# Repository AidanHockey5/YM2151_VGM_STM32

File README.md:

# This project has been superseded by...
https://github.com/AidanHockey5/YM2151_Arcade_Classic_2

# YM2151 Arcade Classic

http://www.aidanlawrence.com/ym2151-arcade-classic-adlib-mini/

See this project in action here: https://youtu.be/VlT8aX9DRZw

This project is a hardware Video Game Music (VGM) player that uses a genuine YM2151 FM synthesizer chip. 
This project is driven by an STM32 "Blue Pill" board, chosen for it's ample speed, I/O, and best of all, price!

Included in this repository is the source code for the project, all of the schematic files, a Bill of Materials, and a completed 
Ki-CAD printed circuitboard /w Gerber files. Feel free to produce your own board!

# Information about the main sound chips and VGM

The YM2151 was a popular sound synthesizer for classic arcade systems as well as a few higher-end home computers in the late 80's and early 90's.
This project synthesizes music from .VGM files in real time on genuine hardware. There is no emulation here.

VGM stands for Video Game Music, and it is a 44.1KHz logging format that stores real soundchip register information. My player will parse these files and send the data to the appropriate chips. You can learn more about the VGM file format here: http://www.smspower.org/Music/VGMFileFormat

http://www.smspower.org/uploads/Music/vgmspec170.txt?sid=58da937e68300c059412b536d4db2ca0

# SD Card Information
This project is built for full-sized SD cards, but you may use adapters to fit your desired card. You must format your SD card to Fat32 in order for this device to work correctly. Your SD card must only contain uncompressed .vgm files. VGZ FILES WILL NOT WORK! You may download .vgz files and use [7zip](http://www.7-zip.org/download.html) to extract the uncompressed file out of them. Vgm files on the SD card do not need to have the .vgm extension. As long as they contain valid, uncompressed vgm data, they will be read by the program regardless of their name.
You can find VGM files by Googling "myGameName VGM," or by checking out sites like http://vgmrips.net/packs/

# Control Over Serial
You can use a serial connection to control playback features. The commands are as follows:

Command | Result
------------ | -------------
\+ | Next Track
\- | Previous Track
\* | Random Track
\/ | Toggle Shuffle Mode
\. | Toggle Song Looping
r: | Request song

A song request is formatted as follows: ```r:mySongFile.vgm```
Once a song request is sent through the serial console, an attempt will be made to open that song file. The file must exist on the SD card, and spelling/capitalization must be correct.
Need an easy-to-use serial console? [I've made one here.](https://github.com/AidanHockey5/OpenArduinoSerialConsole)

# Schematic

[PDF](https://github.com/AidanHockey5/YM2151_VGM_STM32/raw/master/Schematic/YM2151_STM32_VGM.pdf)

[Bill Of Materials (BOM)](https://github.com/AidanHockey5/YM2151_VGM_STM32/tree/master/Schematic/BOM)

# KiCad
The schematic and PCB of this project was made in KiCad Version 4.0.7

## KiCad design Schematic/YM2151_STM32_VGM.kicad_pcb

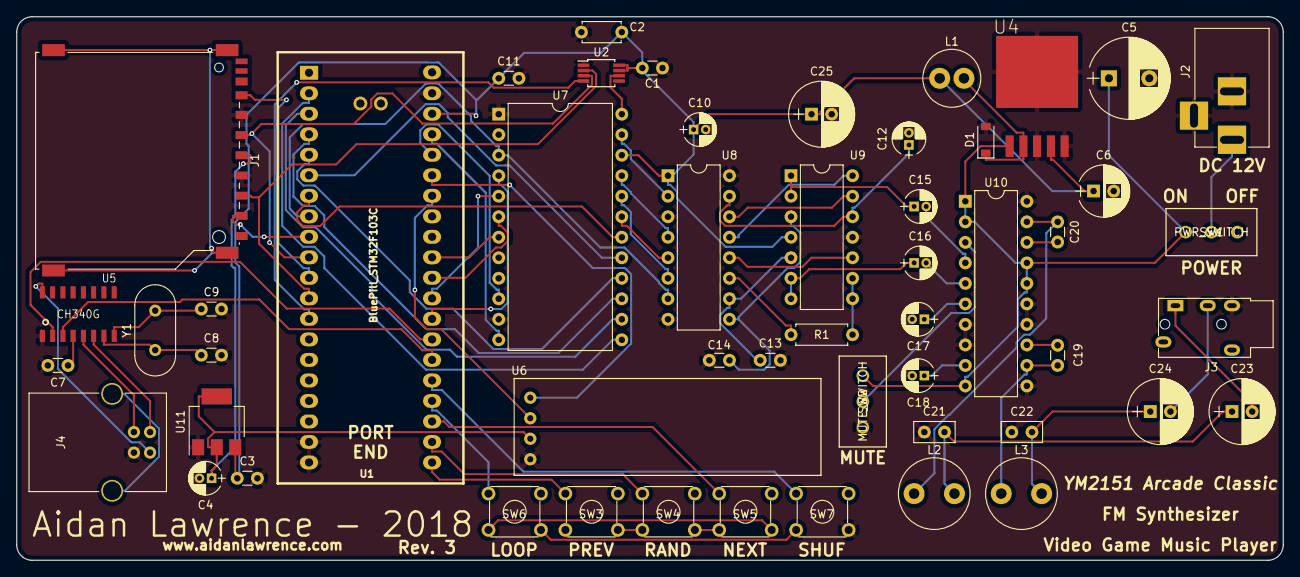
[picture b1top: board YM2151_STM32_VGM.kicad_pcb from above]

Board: 2 copper layers, 156.8 x 67.3 mm, 52 parts (0 on the bottom side), 71 nets.

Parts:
C1: 10nF; C_Disc_D3.0mm_W1.6mm_P2.50mm
C2: 1uF; C_Disc_D4.7mm_W2.5mm_P5.00mm
C3, C7, C11: 100nF; C_Disc_D3.0mm_W1.6mm_P2.50mm
C4, C10, C12: 10uF; CP_Radial_D4.0mm_P1.50mm
C5: 680uF; CP_Radial_D10.0mm_P5.00mm
C6: 220uF; CP_Radial_D6.3mm_P2.50mm
C8, C9: 22pF; C_Disc_D3.0mm_W1.6mm_P2.50mm
C13, C14: 3.3nF; C_Disc_D3.0mm_W1.6mm_P2.50mm
C15, C16, C17, C18: 1uF; CP_Radial_D4.0mm_P1.50mm
C19, C20: 0.22uF; C_Disc_D3.0mm_W1.6mm_P2.50mm
C21, C22: 68nF; C_Disc_D5.0mm_W2.5mm_P2.50mm
C23, C24, C25: 1000uF; CP_Radial_D8.0mm_P2.50mm
D1: SS34; D_SOD-123
J1: SD_Card; SD_TE_2041021
J2: Jack_DC+12V; BARREL_JACK
J3: JACK_TRS_6PINS; PJ320E_3.5mm_Jack
J4: USB_B
L1: 33uH; L_Radial_D7.0mm_P3.00mm
L2, L3: 22uH; L_Radial_D8.7mm_P5.00mm_Fastron_07HCP
R1: 100; R_Axial_DIN0207_L6.3mm_D2.5mm_P7.62mm_Horizontal
SW1: PWR_SWITCH; 1825115-1
SW2: MUTE_SWITCH; 1825115-1
SW3: PREV; SW_TH_Tactile_Omron_B3F-10xx
SW4: RAND; SW_TH_Tactile_Omron_B3F-10xx
SW5: NEXT; SW_TH_Tactile_Omron_B3F-10xx
SW6: LOOP; SW_TH_Tactile_Omron_B3F-10xx
SW7: SHUF; SW_TH_Tactile_Omron_B3F-10xx
U1: BluePill_STM32F103C
U2: LTC6903; MSOP-8_3x3mm_Pitch0.65mm
U4: LM2596S-5.0; TO170P1435X465-6N
U5: CH340G; SOIC16
U6: OLED_128x32_I2C; 128x32_OLED_I2C_Module
U7: YM2151; DIP-24_W15.24mm
U8: YM3012; DIP-16_W7.62mm
U9: TL064; DIP-14_W7.62mm
U10: TPA3122D2; DIP-20_W7.62mm
U11: LD1117; SOT-223-3_TabPin2
Y1: 12MHz; Crystal_HC49-U_Vertical

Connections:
+3V3: C4.1, J1.4, U6.2, U11.2
+5V: C1.1, C2.1, C3.1, C6.1, C10.1, C11.1, C25.1, L1.1, U1.38, U2.7, U2.8, U4.4, U7.22, U8.1, U9.4, U11.3
+12V: C5.1, SW1.1, SW2.3, U4.1, U10.1, U10.2, U10.10, U10.16, U10.17
BC: U8.14, U9.13
CH1: C14.1, U8.9, U9.3
CH2: C13.1, U8.10, U9.5
COM: R1.2, U8.11
D0: U1.36, U7.10
D1: U1.37, U7.12
D2: U1.2, U7.13
D3: U1.3, U7.14
D4: U1.4, U7.15
D5: U1.5, U7.16
D6: U1.6, U7.17
D7: U1.7, U7.18
GND: C1.2, C2.2, C3.2, C4.2, C5.2, C6.2, C7.2, C8.2, C9.2, C10.2, C11.2, C12.2, C13.2, C14.2, C17.2, C18.2, C21.1, C22.2, C25.2, D1.2, J1.3, J1.6, J2.2, J2.3, J3.3, J4.4, SW2.1, SW3.3, SW7.4, U1.19, U1.20, U1.39, U2.1, U4.3, U4.5, U4.6, U5.1, U6.1, U7.1, U7.11, U8.3, U8.8, U8.16, U9.11, U10.7, U10.8, U10.11, U10.14, U10.15, U10.20, U11.1
LEFT_OP_OUT: C15.1, U9.1, U9.2
LOOP: SW6.1, U1.24
L_OUT: C23.2, J3.1
MP: U8.13, U9.14
NEXT: SW5.1, U1.23
unnamed: C7.1, U5.4
unnamed: C8.1, U5.7, Y1.1
unnamed: C9.1, U5.8, Y1.2
unnamed: C15.2, U10.4
unnamed: C16.2, U10.5
unnamed: C17.1, U10.6
unnamed: C18.1, U10.9
unnamed: C19.1, L3.1, U10.12
unnamed: C19.2, U10.13
unnamed: C20.1, L2.1, U10.19
unnamed: C20.2, U10.18
unnamed: C21.2, C23.1, L2.2
unnamed: C22.1, C24.1, L3.2
unnamed: D1.1, L1.2, U4.2
unnamed: J2.1, SW1.2
unnamed: J4.1, U5.16
unnamed: J4.2, U5.6
unnamed: J4.3, U5.5
unnamed: R1.1, U9.8, U9.9
unnamed: SW2.2, U10.3
unnamed: SW3.4, SW4.3
unnamed: SW4.4, SW5.3
unnamed: SW5.4, SW6.3
unnamed: SW6.4, SW7.3
unnamed: U2.6, U7.24
unnamed: U7.23, U8.2
PREV: SW3.1, U1.21
RAND: SW4.1, U1.22
RB: C12.1, U8.15, U9.12
RIGHT_OP_OUT: C16.1, U9.6, U9.7
RX: U1.26, U5.3
R_OUT: C24.2, J3.2
SCL: U1.34, U6.3
SDA: U1.35, U6.4
SD_CS: J1.1, U1.9
SH1: U7.20, U8.6
SH2: U7.19, U8.5
SHUF: SW7.1, U1.25
SO: U7.21, U8.4
SPI_MISO: J1.7, U1.11
SPI_MOSI: J1.2, U1.12, U2.2
SPI_SCLK: J1.5, U1.10, U2.3
TX: U1.27, U5.2
YM_A0: U1.28, U7.4
YM_CLOCK_CS: U1.13, U2.4
YM_CS: U1.31, U7.7
YM_IC: U1.8, U7.3, U8.7
YM_RD: U1.30, U7.6
YM_WR: U1.29, U7.5
tBUF: U8.12, U9.10

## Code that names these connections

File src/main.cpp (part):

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const int loop_btn = PB15;
const int shuf_btn = PA8;
int YM_Datapins[8] = {PB8, PB9, PC13, PC14, PC15, PA0, PA1, PA2};
const int YM_CS = PB3;
const int YM_RD = PA15;
const int YM_WR = PA12;
const int YM_A0 = PA11;
const int YM_IC = PA3; 
const int YM_IRQ = NULL;
YM2151 opm(YM_Datapins, YM_CS, YM_RD, YM_WR, YM_A0, YM_IRQ, YM_IC);

//Clock
LTC6903 ltc(PB0);
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
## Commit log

2018-02-19 Full VGM player for YM2151 with STM32. LTC6903 now supports dynamic clocking.
2018-02-25 Added OLED. Began schematic. Project is feature-complete
2018-02-25 Schematic complete
2018-02-25 In progress of appending footprints
2018-02-25 Footprint selection finalized
2018-02-26 Finalizing PCB
2018-02-26 PCB complete
2018-02-26 Corrected PCB - unconnected GND on LTC6903
2018-03-03 Corrected SD card on schematic and board. Added button control
2018-03-03 Fixed no-clock on startup, added switch debounce
2018-03-03 Added Bill of Materials
2018-03-10 Added catch conditions for VGM commands for common PCM chips.
2018-03-13 Correct clock startup sequence to always start on a safe frequency.
2018-03-15 Now skips data blocks reserved for PCM chips
2018-03-16 Corrected YM2151 reset on startup that would cause garbled sound on first track.
2018-03-25 Update LICENSE
2018-03-31 Added footprint archive
2018-03-31 Added component libraries to local project folder.
2018-03-31 Added headphone jack symbol
2018-05-12 Fixed loop offset
2018-05-19 Added improved BOM
2018-05-19 Update Readme and BOM files
2018-05-19 Updated BOM component references
2018-06-10 Corrected schematic. L2, L3 inductors 22uH->2.2mH
2018-06-10 Correct schematic and BOM. L2 L3 22uH->2.2mH
2018-07-09 Fixed random song crash when only one file is present and fixed occasional start-up clocking failure
2018-07-09 Deactivated INVERTED CLOCK pin on LTC6903
2018-08-14 Repaired headphone jack pinout on PCB.
2018-08-25 Changed private BOM link public cart link
2019-05-27 New VGM driver backported
2019-06-15 BOM correction
2019-08-11 Create LICENSE
2019-08-11 Rename LICENSE to LICENSE.md
2019-08-31 New SD init to remove meta files

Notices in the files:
parts and their libraries:
Copyright 2016 Accelerated Designs. All rights reserved.
